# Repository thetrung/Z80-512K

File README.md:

# Z80-512K 
Z80 system with 512K SRAM/EEPROM & Expansion Bus.

### Note
This one start as independent Z80 system, target at 8Mhz clock & put any I/O into expansion bus instead.

### 3D Preview 

### Placement (SilkScreen)

### Schematic

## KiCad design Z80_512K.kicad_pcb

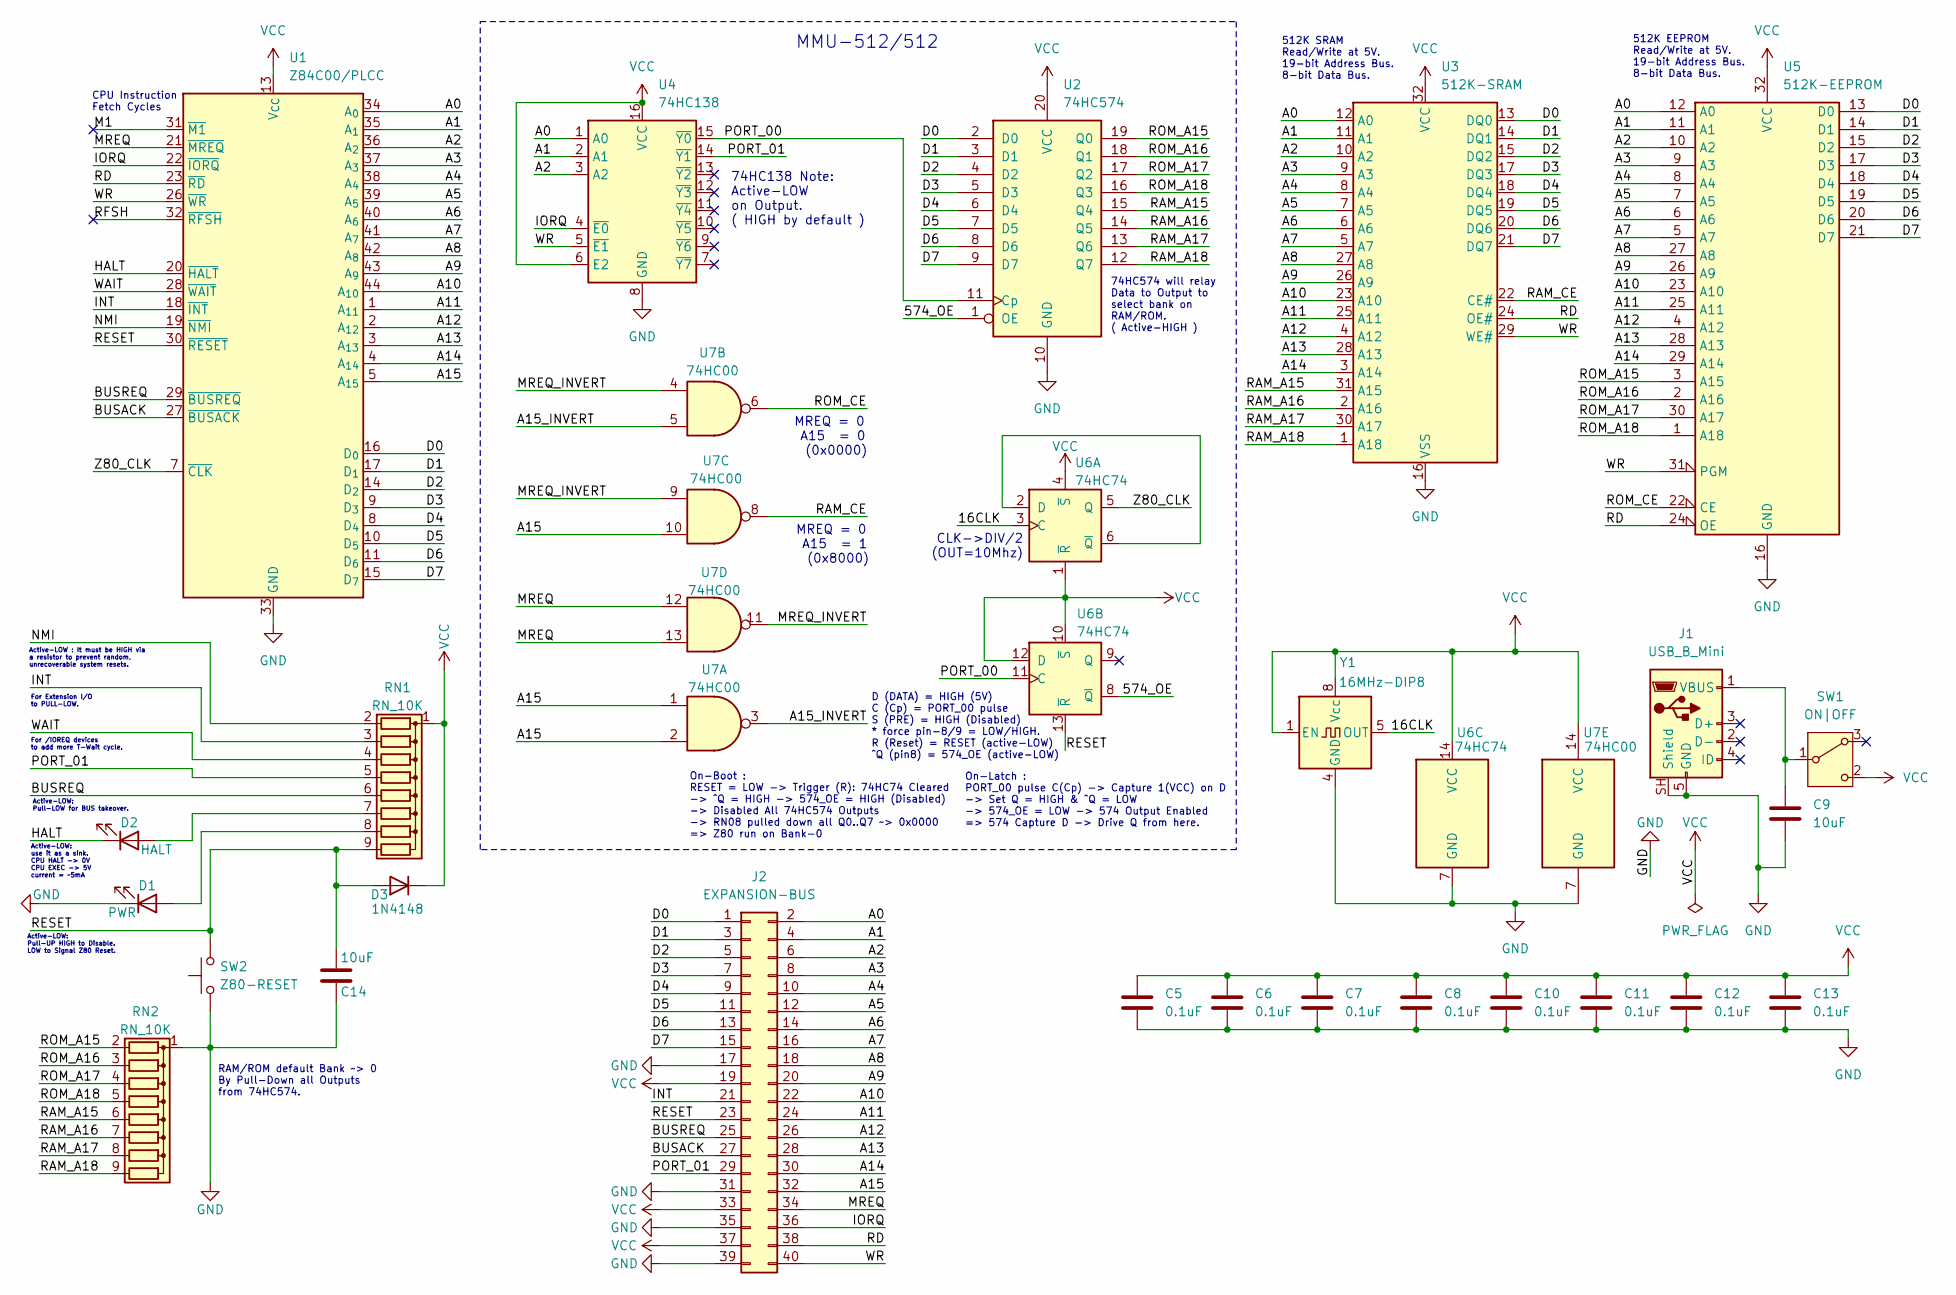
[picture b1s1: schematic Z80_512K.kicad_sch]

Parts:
C5, C6, C7, C8, C10, C11, C12, C13: 0.1uF; C_Disc_D3.4mm_W2.1mm_P2.50mm
C9, C14: 10uF; C_Radial_D4.0mm_H5.0mm_P1.50mm
D1: PWR; LED_D3.0mm
D2: HALT; LED_D3.0mm
D3: 1N4148; D_DO-35_SOD27_P7.62mm_Horizontal
J1: USB_B_Mini; USB_MINI_B_90_Angled
J2: EXPANSION-BUS; PinHeader_2x20_P2.54mm_Horizontal
RN1, RN2: RN_10K; R_Array_SIP9
SW1: ON|OFF; SW_Slide-03_Wuerth-WS-SLTV_10x2.5x6.4_P2.54mm
SW2: Z80-RESET; SW_PUSH_6mm
U1: Z84C00/PLCC; PLCC-44_THT-Socket
U2: 74HC574; DIP-20_W7.62mm
U3: 512K-SRAM; DIP-32_W15.24mm
U4: 74HC138; DIP-16_W7.62mm
U5: 512K-EEPROM; DIP-32_W15.24mm
U6: 74HC74; DIP-14_W7.62mm
U7: 74HC00; DIP-14_W7.62mm
Y1: 16MHz-DIP8; Oscillator_DIP-8

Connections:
/16CLK: U6.3 (C), Y1.5 (OUT)
/574_OE: U2.1 (OE), U6.8 (~Q)
/A0: J2.2, U1.34 (A_{0}), U3.12 (A0), U4.1 (A0), U5.12 (A0)
/A1: J2.4, U1.35 (A_{1}), U3.11 (A1), U4.2 (A1), U5.11 (A1)
/A2: J2.6, U1.36 (A_{2}), U3.10 (A2), U4.3 (A2), U5.10 (A2)
/A3: J2.8, U1.37 (A_{3}), U3.9 (A3), U5.9 (A3)
/A4: J2.10, U1.38 (A_{4}), U3.8 (A4), U5.8 (A4)
/A5: J2.12, U1.39 (A_{5}), U3.7 (A5), U5.7 (A5)
/A6: J2.14, U1.40 (A_{6}), U3.6 (A6), U5.6 (A6)
/A7: J2.16, U1.41 (A_{7}), U3.5 (A7), U5.5 (A7)
/A8: J2.18, U1.42 (A_{8}), U3.27 (A8), U5.27 (A8)
/A9: J2.20, U1.43 (A_{9}), U3.26 (A9), U5.26 (A9)
/A10: J2.22, U1.44 (A_{10}), U3.23 (A10), U5.23 (A10)
/A11: J2.24, U1.1 (A_{11}), U3.25 (A11), U5.25 (A11)
/A12: J2.26, U1.2 (A_{12}), U3.4 (A12), U5.4 (A12)
/A13: J2.28, U1.3 (A_{13}), U3.28 (A13), U5.28 (A13)
/A14: J2.30, U1.4 (A_{14}), U3.3 (A14), U5.29 (A14)
/A15: J2.32, U1.5 (A_{15}), U7.1, U7.2, U7.10
/A15_INVERT: U7.3, U7.5
/BUSACK: J2.27, U1.27 (~BUSACK)
/BUSREQ: J2.25, RN1.6 (R5), U1.29 (~BUSREQ)
/D0: J2.1, U1.16 (D_{0}), U2.2 (D0), U3.13 (DQ0), U5.13 (D0)
/D1: J2.3, U1.17 (D_{1}), U2.3 (D1), U3.14 (DQ1), U5.14 (D1)
/D2: J2.5, U1.14 (D_{2}), U2.4 (D2), U3.15 (DQ2), U5.15 (D2)
/D3: J2.7, U1.9 (D_{3}), U2.5 (D3), U3.17 (DQ3), U5.17 (D3)
/D4: J2.9, U1.8 (D_{4}), U2.6 (D4), U3.18 (DQ4), U5.18 (D4)
/D5: J2.11, U1.10 (D_{5}), U2.7 (D5), U3.19 (DQ5), U5.19 (D5)
/D6: J2.13, U1.11 (D_{6}), U2.8 (D6), U3.20 (DQ6), U5.20 (D6)
/D7: J2.15, U1.15 (D_{7}), U2.9 (D7), U3.21 (DQ7), U5.21 (D7)
/HALT: D2.1 (K), U1.20 (~HALT)
/INT: J2.21, RN1.3 (R2), U1.18 (~INT)
/IORQ: J2.36, U1.22 (~IORQ), U4.4 (~E0)
/M1: U1.31 (~M1)
/MREQ: J2.34, U1.21 (~MREQ), U7.12, U7.13
/MREQ_INVERT: U7.4, U7.9, U7.11
/NMI: RN1.2 (R1), U1.19 (~NMI)
/PORT_00: U2.11 (Cp), U4.15 (~Y0), U6.11 (C)
/PORT_01: J2.29, RN1.5 (R4), U4.14 (~Y1)
/RAM_A15: RN2.6 (R5), U2.15 (Q4), U3.31 (A15)
/RAM_A16: RN2.7 (R6), U2.14 (Q5), U3.2 (A16)
/RAM_A17: RN2.8 (R7), U2.13 (Q6), U3.30 (A17)
/RAM_A18: RN2.9 (R8), U2.12 (Q7), U3.1 (A18)
/RAM_CE: U3.22 (CE#), U7.8
/RD: J2.38, U1.23 (~RD), U3.24 (OE#), U5.24 (OE)
/RESET: C14.1, D3.2 (A), J2.23, RN1.9 (R8), SW2.2, U1.30 (~RESET), U6.13 (~R)
/RFSH: U1.32 (~RFSH)
/ROM_A15: RN2.2 (R1), U2.19 (Q0), U5.3 (A15)
/ROM_A16: RN2.3 (R2), U2.18 (Q1), U5.2 (A16)
/ROM_A17: RN2.4 (R3), U2.17 (Q2), U5.30 (A17)
/ROM_A18: RN2.5 (R4), U2.16 (Q3), U5.1 (A18)
/ROM_CE: U5.22 (CE), U7.6
/WAIT: RN1.4 (R3), U1.28 (~WAIT)
/WR: J2.40, U1.26 (~WR), U3.29 (WE#), U4.5 (~E1), U5.31 (PGM)
/Z80_CLK: U1.7 (~CLK), U6.5 (Q)
GND: C5.1, C6.1, C7.1, C8.1, C9.1, C10.1, C11.1, C12.1, C13.1, C14.2, D1.1 (K), J1.5 (GND), J1.SH (Shield), J2.17, J2.31, J2.35, J2.39, RN2.1 (common), SW2.1, U1.33 (GND), U2.10 (GND), U3.16 (VSS), U4.8 (GND), U5.16 (GND), U6.7 (GND), U7.7 (GND), Y1.4 (GND)
unnamed: D1.2 (A), RN1.8 (R7)
unnamed: D2.2 (A), RN1.7 (R6)
unnamed: C9.2, J1.1 (VBUS), SW1.1 (B)
unnamed: U6.2 (D), U6.6 (~Q)
VCC: C5.2, C6.2, C7.2, C8.2, C10.2, C11.2, C12.2, C13.2, D3.1 (K), J2.19, J2.33, J2.37, RN1.1 (common), SW1.2 (C), U1.13 (V_{CC}), U2.20 (VCC), U3.32 (VCC), U4.6 (E2), U4.16 (VCC), U5.32 (VCC), U6.1 (~R), U6.4 (~S), U6.10 (~S), U6.12 (D), U6.14 (VCC), U7.14 (VCC), Y1.1 (EN), Y1.8 (Vcc)

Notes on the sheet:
MREQ = 0 A15 = 0 (0x0000)
RAM/ROM default Bank ~> 0 By Pull-Down all Outputs from 74HC574.
For /IOREQ devices to add more T-Wait cycle.
512K SRAM Read/Write at 5V. 19-bit Address Bus. 8-bit Data Bus.
Active-LOW: use it as a sink. CPU HALT -> 0V CPU EXEC -> 5V current = ~5mA
CLK->DIV/2 (OUT=10Mhz)
For Extension I/O to PULL-LOW.
74HC138 Note: Active-LOW on Output. ( HIGH by default )
D (DATA) = HIGH (5V) C (Cp) = PORT_00 pulse S (PRE) = HIGH (Disabled) * force pin-8/9 = LOW/HIGH. R (Reset) = RESET (active-LOW) ^Q (pin8) = 574_OE (active-LOW)
512K EEPROM Read/Write at 5V. 19-bit Address Bus. 8-bit Data Bus.
On-Boot : RESET = LOW -> Trigger (R): 74HC74 Cleared -> ^Q = HIGH -> 574_OE = HIGH (Disabled) -> Disabled All 74HC574 Outputs -> RN08 pulled down all Q0..Q7 ~> 0x0000 => Z80 run on Bank-0
Active-LOW : It must be HIGH via a resistor to prevent random, unrecoverable system resets.
Active-LOW: Pull-UP HIGH to Disable. LOW to Signal Z80 Reset.
On-Latch : PORT_00 pulse C(Cp) -> Capture 1(VCC) on D -> Set Q = HIGH & ^Q = LOW -> 574_OE = LOW -> 574 Output Enabled => 574 Capture D -> Drive Q from here.
74HC574 will relay Data to Output to select bank on RAM/ROM. ( Active-HIGH )
CPU Instruction Fetch Cycles
Active-LOW: Pull-LOW for BUS takeover.
MREQ = 0 A15 = 1 (0x8000)
MMU-512/512

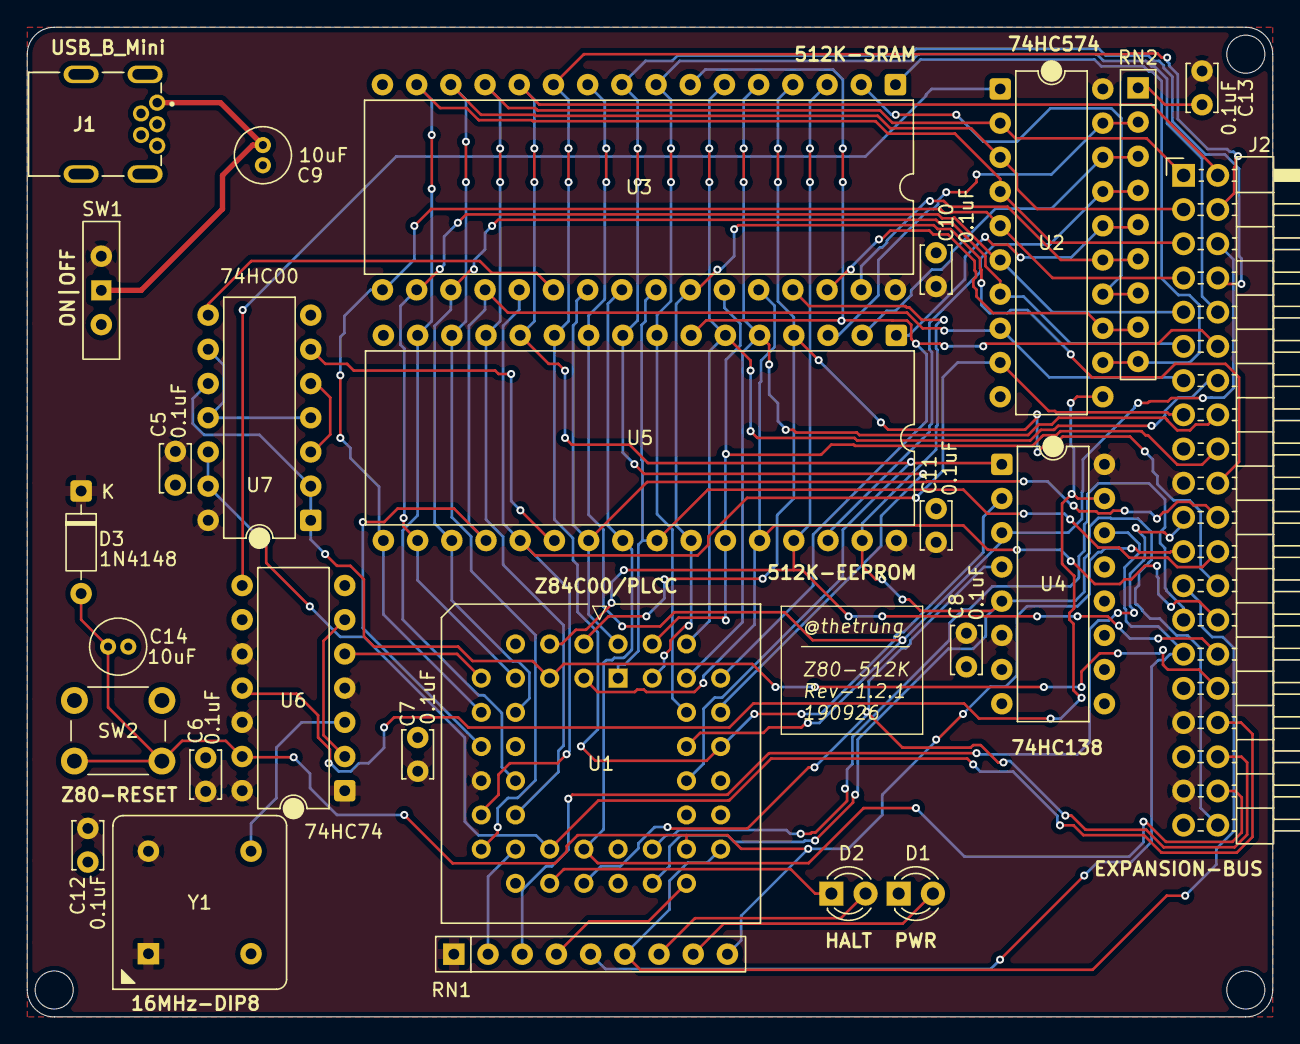
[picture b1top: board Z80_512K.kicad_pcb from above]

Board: 2 copper layers, 92.5 x 73.5 mm, 27 parts (0 on the bottom side), 58 nets.
